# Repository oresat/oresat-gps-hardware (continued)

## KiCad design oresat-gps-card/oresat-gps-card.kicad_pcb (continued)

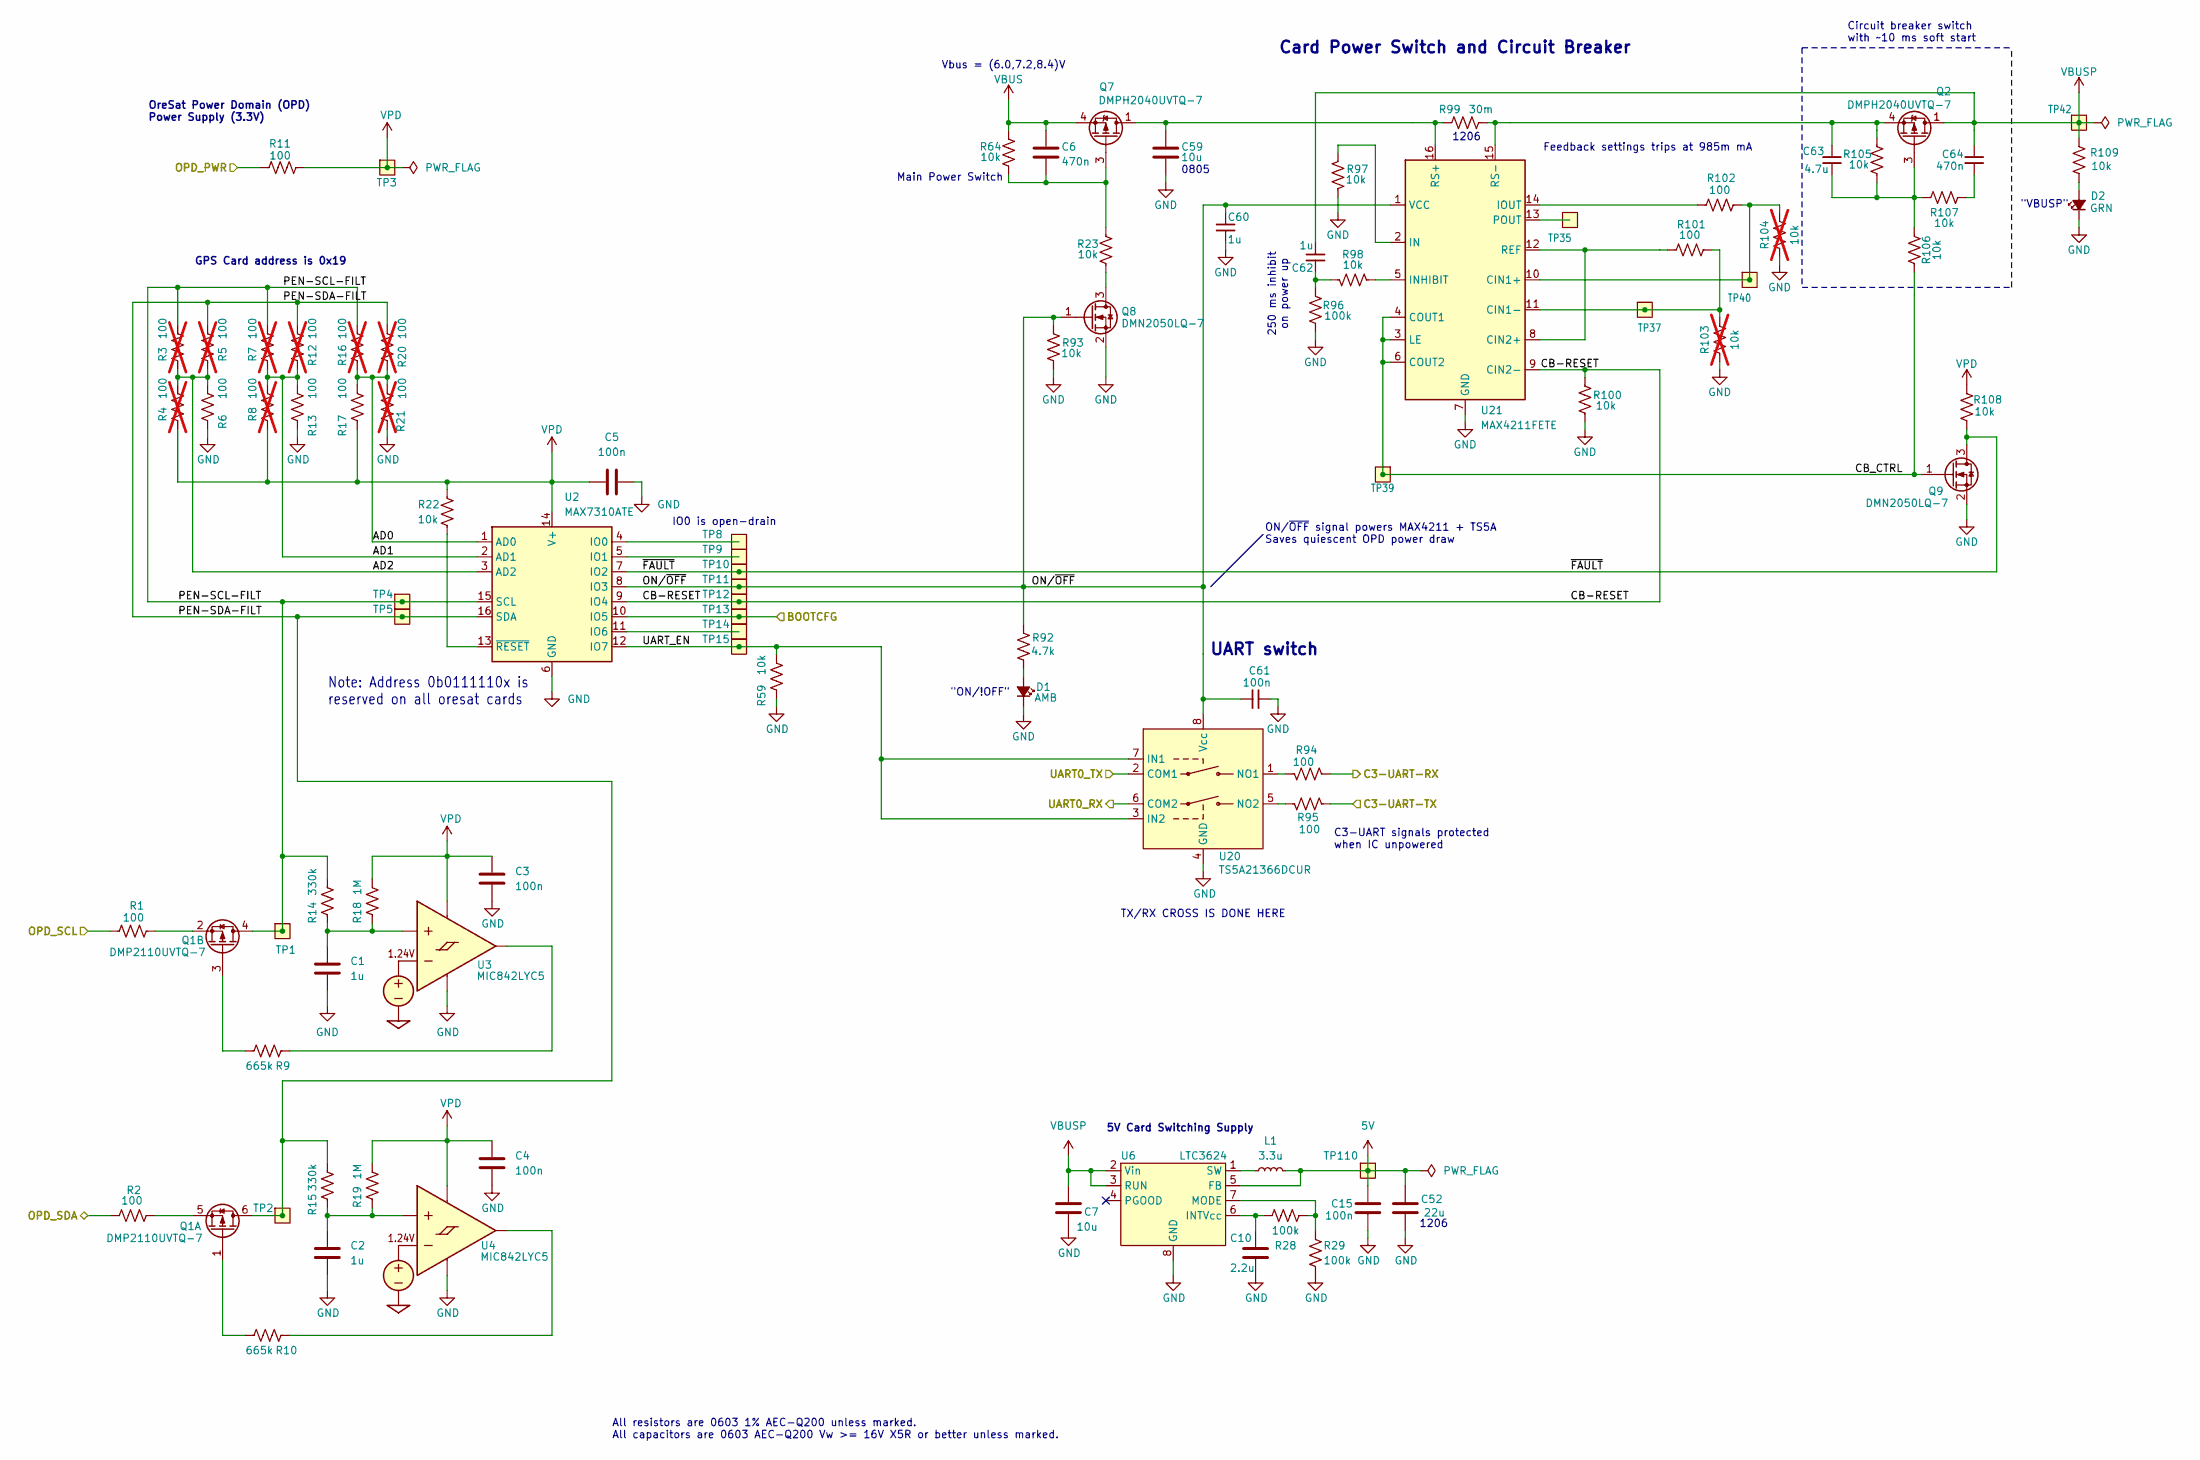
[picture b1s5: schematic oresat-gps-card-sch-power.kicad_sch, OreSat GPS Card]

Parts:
C1, C2, C60, C62: 1u; 0603-C-NOSILK; MPN GRT188R71E105KE13D
C3, C4, C5, C15, C61: 100n; 0603-C-NOSILK; MPN C0603C104K5RACAUTO
C6, C64: 470n; 0603-C-NOSILK; MPN C0603C474K3RACAUTO
C7: 10u; 0805-C-NOSILK; MPN GRT21BC71E106KE13K
C10: 2.2u; 0603-C-NOSILK; MPN GRT188C71E225KE13D
C52: 22u; C_1206_3216Metric; MPN GRT31CC81C226KE01L
C59: 10u; 0805-B-NOSILK; MPN GRT21BC71E106KE13K
C63: 4.7u; 0603-C-NOSILK; MPN GRT21BC71E475KE13L
D1: AMB; LED_0603_1608Metric; MPN 150060AS75000
D2: GRN; LED_0603_1608Metric; MPN 150060GS75000
L1: 3.3u; L_ECS-MPI4040; MPN ECS-MPIP0420-3R3MC
Q1: DMP2110UVTQ-7; SOT-23-6; MPN DMP2110UVTQ-7
Q2, Q7: DMPH2040UVTQ-7; TSOT-23-6; MPN DMPH2040UVTQ-7
Q8, Q9: DMN2050LQ-7; SOT-23; MPN DMN2050LQ-7
R1, R2, R6, R11, R13, R17, R94, R95, R101, R102: 100; 0603-C-NOSILK; MPN RMCF0603FT100R
R3, R4, R5, R7, R8, R12, R16, R20, R21: 100; 0603-C-NOSILK; not fitted
R9, R10: 665k; 0603-C-NOSILK; MPN RMCF0603FT665K
R14, R15: 330k; 0603-C-NOSILK; MPN RMCF0603FT330K
R18, R19: 1M; 0603-C-NOSILK; MPN RMCF0603FT1M00
R22, R23, R59, R64, R93, R97, R98, R100, R105, R106, R107, R108, R109: 10k; 0603-C-NOSILK; MPN RMCF0603FT10K0
R28, R29, R96: 100k; 0603-C-NOSILK; MPN RMCF0603FT100K
R92: 4.7k; 0603-C-NOSILK; MPN RMCF0603FT4K70
R99: 30m; 1206-C; MPN CSR1206FK30L0
R103, R104: 10k; 0603-C-NOSILK; MPN RMCF0603FT10K0; not fitted
TP1, TP2, TP3, TP4, TP5, TP8, TP9, TP10, TP11, TP12, TP13, TP14, TP15, TP35, TP37, TP39, TP40, TP42, TP110: Test-Point; TestPoint-0.75mm-th
U2: MAX7310ATE; QFN-16-1EP_4x4mm_P0.65mm_EP2.1x2.1mm; MPN MAX7310ATE+
U3, U4: MIC842LYC5; SOT-353_SC-70-5; MPN MIC842LYC5-TR
U6: LTC3624; DFN-8-1EP_3x3mm_P0.5mm_EP1.65x2.38mm_ThermalVias0.3mm; MPN LTC3624IDD-5#PBF
U20: TS5A21366DCUR; VSSOP-8_2.3x2mm_P0.5mm; MPN TS5A21366DCUR
U21: MAX4211FETE; QFN-16-1EP_4x4mm_P0.65mm_EP2.1x2.1mm; MPN MAX4211FETE

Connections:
5V: C15.1, C52.1, L1.2, TP110.1 (1_1), U6.5 (FB); also elsewhere on the board
/C3-UART-RX: R94.1; also elsewhere on the board
/C3-UART-TX: R95.1; also elsewhere on the board
/OPD_PWR: R11.1; also elsewhere on the board
/OPD_SCL: R1.1; also elsewhere on the board
/OPD_SDA: R2.1; also elsewhere on the board
/OSD3358 SYSBOOT : SIP D/BOOTCFG: TP13.1 (1_1), U2.10 (IO5); also elsewhere on the board
/Power/AD0: R16.2, R17.1, R20.2, R21.1, U2.1 (AD0)
/Power/AD1: R7.2, R8.1, R12.2, R13.1, U2.2 (AD1)
/Power/AD2: R3.2, R4.1, R5.2, R6.1, U2.3 (AD2)
/Power/CB-RESET: R100.2, TP12.1 (1_1), U2.9 (IO4), U21.9 (CIN2-)
/Power/CB_CTRL: Q9.1 (G), R106.1, TP39.1 (1_1), U21.3 (LE), U21.4 (COUT1), U21.6 (COUT2)
/Power/ON/~OFF: C60.1, C61.2, Q8.1 (G), R92.1, R93.2, TP11.1 (1_1), U2.8 (IO3), U20.8 (Vcc), U21.1 (VCC)
/Power/PEN-SCL-FILT: Q1.4 (D), R3.1, R7.1, R14.2, R16.1, TP1.1 (1_1), TP4.1 (1_1), U2.15 (SCL)
/Power/PEN-SDA-FILT: Q1.6 (D), R5.1, R12.1, R15.2, R20.1, TP2.1 (1_1), TP5.1 (1_1), U2.16 (SDA)
/Power/UART_EN: R59.2, TP15.1 (1_1), U2.12 (IO7), U20.3 (IN2), U20.7 (IN1)
/Power/~FAULT: Q9.3 (D), R108.1, TP10.1 (1_1), U2.7 (IO2)
/UART0_RX: U20.6 (COM2); also elsewhere on the board
/UART0_TX: U20.2 (COM1); also elsewhere on the board
GND: C1.1, C2.1, C3.1, C4.1, C5.2, C7.2, C10.2, C15.2, C52.2, C59.2, C60.2, C61.1, D1.1 (K), D2.1 (K), Q8.2 (S), Q9.2 (S), R6.2, R13.2, R21.2, R29.2, R59.1, R93.1, R96.1, R97.2, R100.1, R103.1, R104.1, U2.6 (GND), U2.17 (GND), U3.2 (GND), U4.2 (GND), U6.8 (GND), U6.9 (GND), U20.4 (GND), U21.7 (GND), U21.17 (GND); also elsewhere on the board
unnamed: C62.1, R96.2, R98.2
unnamed: C64.1, R107.1
unnamed: D1.2 (A), R92.2
unnamed: D2.2 (A), R109.1
unnamed: Q1.1 (G), R10.2
unnamed: Q1.5 (S), R2.2
unnamed: Q1.3 (G), R9.2
unnamed: Q1.2 (S), R1.2
unnamed: C63.1, Q2.3 (G), R105.1, R106.2, R107.2
unnamed: C63.2, Q2.4 (S), R99.2, R105.2, U21.15 (RS-)
unnamed: C6.2, Q7.3 (G), R23.2, R64.1
unnamed: Q8.3 (D), R23.1
unnamed: TP8.1 (1_1), U2.4 (IO0)
unnamed: TP9.1 (1_1), U2.5 (IO1)
unnamed: TP14.1 (1_1), U2.11 (IO6)
unnamed: R22.2, U2.13 (~RESET)
unnamed: C1.2, R14.1, R18.1, U3.1 (INP)
unnamed: R9.1, U3.4 (OUT)
unnamed: C2.2, R15.1, R19.1, U4.1 (INP)
unnamed: R10.1, U4.4 (OUT)
unnamed: C10.1, R28.1, U6.6 (INTVcc)
unnamed: R28.2, R29.1, U6.7 (MODE)
unnamed: L1.1, U6.1 (SW)
unnamed: R94.2, U20.1 (NO1)
unnamed: R95.2, U20.5 (NO2)
unnamed: R102.1, R104.2, TP40.1 (1_1), U21.10 (CIN1+)
unnamed: R101.1, R103.2, TP37.1 (1_1), U21.11 (CIN1-)
unnamed: R101.2, U21.8 (CIN2+), U21.12 (REF)
unnamed: R97.1, U21.2 (IN)
unnamed: R98.1, U21.5 (INHIBIT)
unnamed: R102.2, U21.14 (IOUT)
unnamed: TP35.1 (1_1), U21.13 (POUT)
unnamed: C59.1, Q7.1 (D), Q7.2 (D), Q7.5 (D), Q7.6 (D), R99.1, U21.16 (RS+)
VBUS: C6.1, Q7.4 (S), R64.2; also elsewhere on the board
VBUSP: C7.1, C62.2, C64.2, Q2.1 (D), Q2.2 (D), Q2.5 (D), Q2.6 (D), R109.2, TP42.1 (1_1), U6.2 (Vin), U6.3 (RUN)
VPD: C3.2, C4.2, C5.1, R4.2, R8.2, R11.2, R17.2, R18.2, R19.2, R22.1, R108.2, TP3.1 (1_1), U2.14 (V+), U3.5 (VDD), U4.5 (VDD)

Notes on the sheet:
Circuit breaker switch with ~10 ms soft start
Main Power Switch
5V Card Switching Supply
IO0 is open-drain
OreSat Power Domain (OPD) Power Supply (3.3V)
Feedback settings trips at 985m mA
TX/RX CROSS IS DONE HERE
"ON/!OFF"
1206
Vbus = (6.0,7.2,8.4)V
Note: Address 0b0111110x is reserved on all oresat cards
0805
GPS Card address is 0x19
C3-UART signals protected when IC unpowered
All resistors are 0603 1% AEC-Q200 unless marked. All capacitors are 0603 AEC-Q200 Vw >= 16V X5R or better unless marked.
"VBUSP"
Card Power Switch and Circuit Breaker
250 ms inhibit on power up
UART switch
ON/~{OFF} signal powers MAX4211 + TS5A Saves quiescent OPD power draw

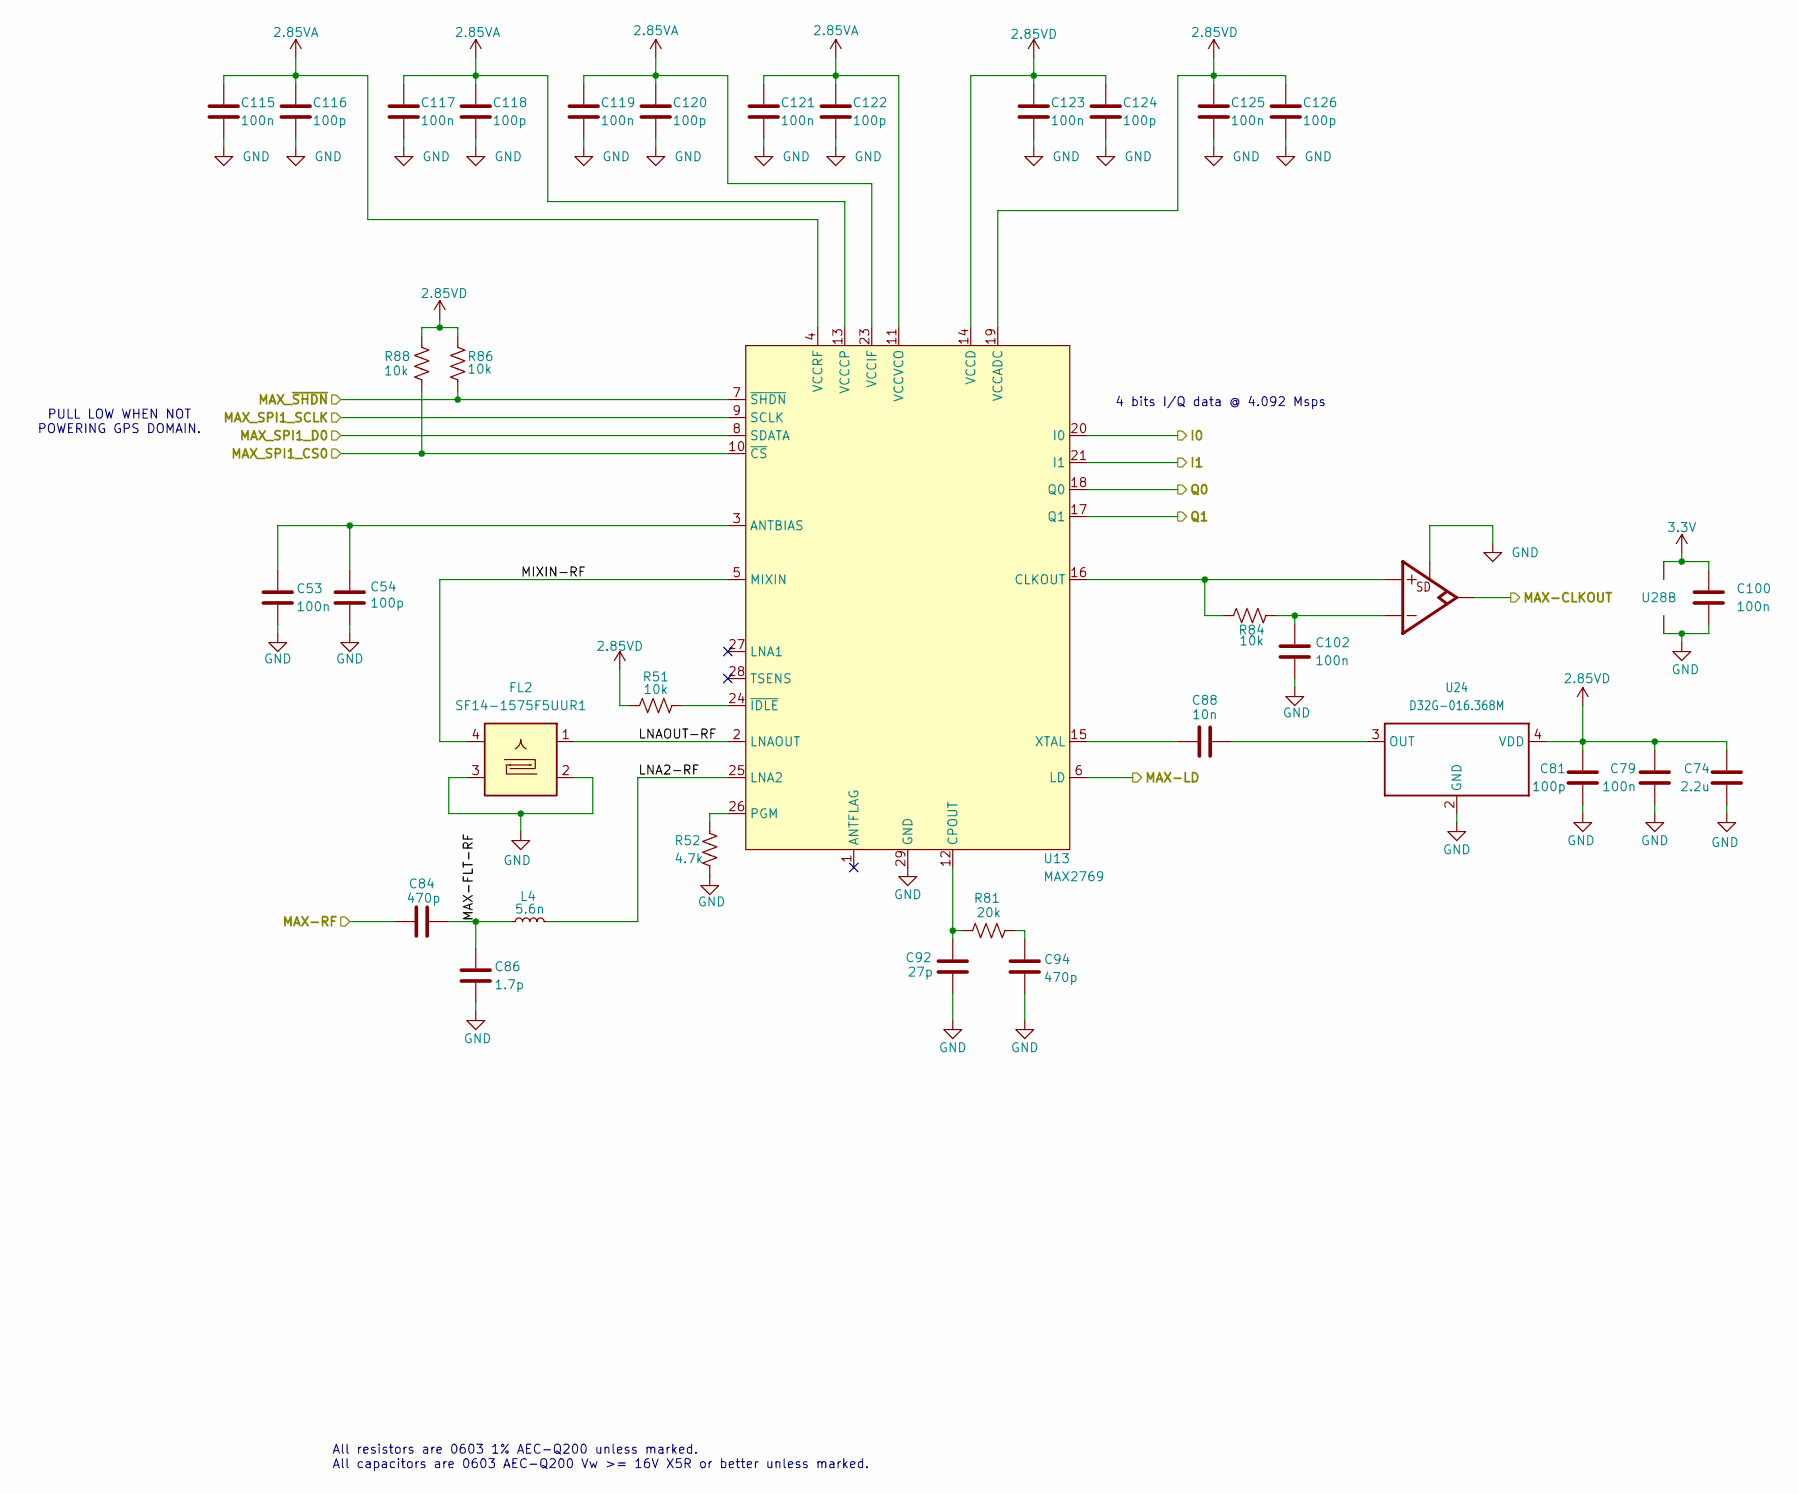
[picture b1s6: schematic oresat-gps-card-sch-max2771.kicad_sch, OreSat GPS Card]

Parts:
C53, C79, C100, C102, C115, C117, C119, C121, C123, C125: 100n; 0603-C-NOSILK; MPN C0603C104K5RACAUTO
C54, C81, C116, C118, C120, C122, C124, C126: 100p; 0603-C-NOSILK; MPN C0603C101K5HACAUTO
C74: 2.2u; 0603-C-NOSILK; MPN GRT188C71E225KE13D
C84, C94: 470p; 0603-C-NOSILK; MPN C0603C471K5RACAUTO
C86: 1.7p; 0603-C-NOSILK; MPN GRM1885C1H1R7BA01D
C88: 10n; 0603-C-NOSILK; MPN C0603C103J5RACAUTO
C92: 27p; 0603-C-NOSILK; MPN GCM1885C2A270JA16D
FL2: SF14-1575F5UUR1; Filter_1411-5_1.4x1.1mm; MPN SF14-1575F5UUR1
L4: 5.6n; 0603-C-NOSILK; MPN LQG18HN5N6S00D
R51, R84, R86, R88: 10k; 0603-C-NOSILK; MPN RMCF0603FT10K0
R52: 4.7k; 0603-C-NOSILK; MPN RMCF0603FT4K70
R81: 20k; 0603-C-NOSILK; MPN RMCF0603FT20K0
U13: MAX2769; TQFN-28-1EP_5x5mm_P0.5mm_EP3.25x3.25mm; MPN MAX2769BETI/V+T
U24: D32G-016.368M; U-Connor-Winfield-D32G-016368M
U28: LT1719IS6; SOT-23-6

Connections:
2.85VA: C115.1, C116.1, C117.1, C118.1, C119.1, C120.1, C121.1, C122.1, U13.4 (VCCRF), U13.11 (VCCVCO), U13.13 (VCCCP), U13.23 (VCCIF); also elsewhere on the board
2.85VD: C74.1, C79.1, C81.1, C123.1, C124.1, C125.1, C126.1, R51.1, R86.1, R88.2, U13.14 (VCCD), U13.19 (VCCADC), U24.4 (VDD); also elsewhere on the board
3.3V: C100.1, U28.4 (V+); also elsewhere on the board
/MAX2769/I0: U13.20 (I0); also elsewhere on the board
/MAX2769/I1: U13.21 (I1); also elsewhere on the board
/MAX2769/LNA2-RF: L4.2, U13.25 (LNA2)
/MAX2769/LNAOUT-RF: FL2.1, U13.2 (LNAOUT)
/MAX2769/MAX-CLKOUT: U28.5 (OUT); also elsewhere on the board
/MAX2769/MAX-FLT-RF: C84.2, C86.1, L4.1
/MAX2769/MAX-LD: U13.6 (LD); also elsewhere on the board
/MAX2769/MAX-RF: C84.1; also elsewhere on the board
/MAX2769/MAX_SPI1_CS0: R88.1, U13.10 (~CS); also elsewhere on the board
/MAX2769/MAX_SPI1_D0: U13.8 (SDATA); also elsewhere on the board
/MAX2769/MAX_SPI1_SCLK: U13.9 (SCLK); also elsewhere on the board
/MAX2769/MAX_~SHDN: R86.2, U13.7 (~SHDN); also elsewhere on the board
/MAX2769/MIXIN-RF: FL2.4, U13.5 (MIXIN)
/MAX2769/Q0: U13.18 (Q0); also elsewhere on the board
/MAX2769/Q1: U13.17 (Q1); also elsewhere on the board
GND: C53.2, C54.2, C74.2, C79.2, C81.2, C86.2, C92.1, C94.1, C100.2, C102.2, C115.2, C116.2, C117.2, C118.2, C119.2, C120.2, C121.2, C122.2, C123.2, C124.2, C125.2, C126.2, FL2.2, FL2.3, FL2.5, R52.2, U13.29 (GND), U24.2 (GND), U28.2 (V-), U28.6 (SD); also elsewhere on the board
unnamed: C94.2, R81.1
unnamed: C53.1, C54.1, U13.3 (ANTBIAS)
unnamed: R84.2, U13.16 (CLKOUT), U28.3 (+IN)
unnamed: C92.2, R81.2, U13.12 (CPOUT)
unnamed: R52.1, U13.26 (PGM)
unnamed: C88.2, U13.15 (XTAL)
unnamed: R51.2, U13.24 (~IDLE)
unnamed: C88.1, U24.3 (OUT)
unnamed: C102.1, R84.1, U28.1 (-IN)

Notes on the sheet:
All resistors are 0603 1% AEC-Q200 unless marked. All capacitors are 0603 AEC-Q200 Vw >= 16V X5R or better unless marked.
PULL LOW WHEN NOT POWERING GPS DOMAIN.
4 bits I/Q data @ 4.092 Msps

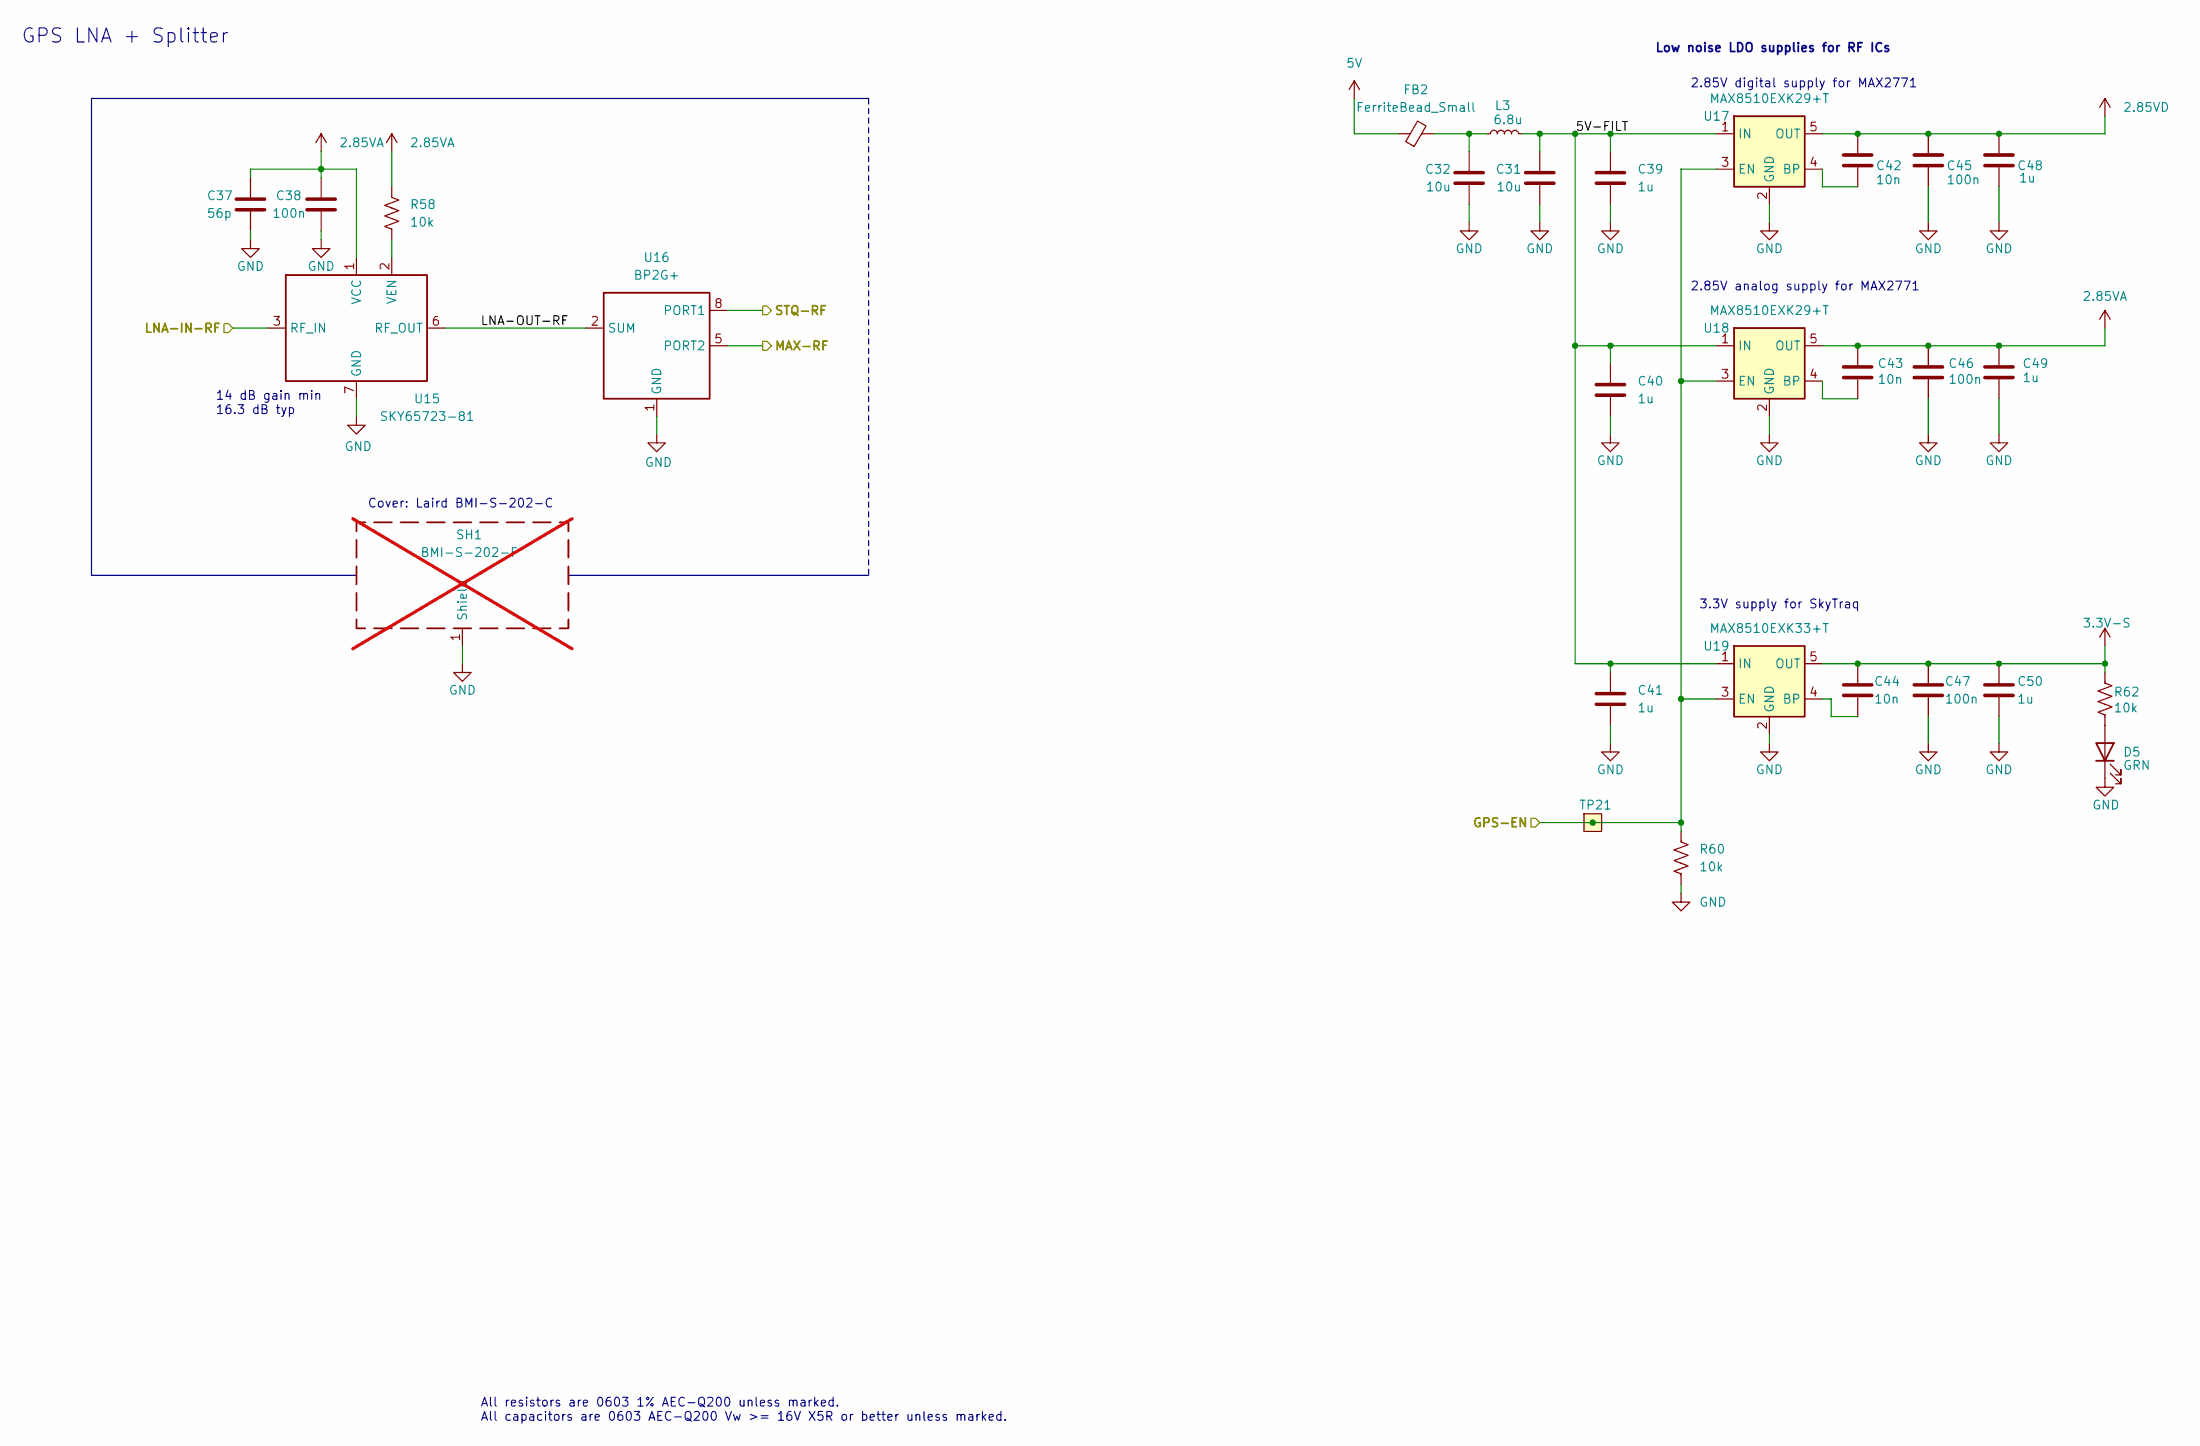
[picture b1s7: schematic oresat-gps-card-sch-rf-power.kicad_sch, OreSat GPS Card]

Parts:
C31, C32: 10u; 0805-C-NOSILK; MPN GRT21BC71E106KE13K
C37: 56p; 0603-C-NOSILK; MPN GRM1885C2A560JA01D
C38, C45, C46, C47: 100n; 0603-C-NOSILK; MPN C0603C104K5RACAUTO
C39, C40, C41, C48, C49, C50: 1u; 0603-C-NOSILK; MPN GRT188R71E105KE13D
C42, C43, C44: 10n; 0603-C-NOSILK; MPN C0603C103J5RACAUTO
D5: GRN; LED_0603_1608Metric; MPN 150060GS75000
FB2: FerriteBead_Small; 0805-C-NOSILK; MPN BLM21PG331SN1D
L3: 6.8u; L_ECS-MPI4040; MPN ECS-MPIP0420-6R8MC
R58, R60, R62: 10k; 0603-C-NOSILK; MPN RMCF0603FT10K0
SH1: BMI-S-202-F; Laird_Technologies_BMI-S-202-F_16.50x16.50mm; MPN BMI-S-202-F; not fitted
TP21: Test-Point; TestPoint-0.75mm-th
U15: SKY65723-81; U-Skyworks-SKY65723-81-gps-lna; MPN SKY65723-81
U16: BP2G+; U-Minicircuits-BP2G+; MPN BP2G1+
U17, U18: MAX8510EXK29+T; SOT-353_SC-70-5; MPN MAX8510EXK29+T
U19: MAX8510EXK33+T; SOT-353_SC-70-5; MPN MAX8510EXK33+T

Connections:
2.85VA: C37.1, C38.1, C43.1, C46.1, C49.1, R58.1, U15.1 (VCC), U18.5 (OUT); also elsewhere on the board
2.85VD: C42.1, C45.1, C48.1, U17.5 (OUT); also elsewhere on the board
3.3V-S: C44.1, C47.1, C50.1, R62.2, U19.5 (OUT); also elsewhere on the board
5V: FB2.1; also elsewhere on the board
/LNA-IN-RF: U15.3 (RF_IN); also elsewhere on the board
/MAX2769/MAX-RF: U16.5 (PORT2); also elsewhere on the board
/OSD3358 SYSBOOT : SIP D/GPS-EN: R60.1, TP21.1 (1_1), U17.3 (EN), U18.3 (EN), U19.3 (EN); also elsewhere on the board
/RF + RF Power/5V-FILT: C31.1, C39.1, C40.1, C41.1, L3.2, U17.1 (IN), U18.1 (IN), U19.1 (IN)
/RF + RF Power/LNA-OUT-RF: U15.6 (RF_OUT), U16.2 (SUM)
/RF + RF Power/STQ-RF: U16.8 (PORT1); also elsewhere on the board
GND: C31.2, C32.2, C37.2, C38.2, C39.2, C40.2, C41.2, C45.2, C46.2, C47.2, C48.2, C49.2, C50.2, D5.1 (K), R60.2, SH1.1 (Shield_1), U15.7 (GND), U16.1 (GND), U16.3 (GND), U16.4 (GND), U16.6 (GND), U16.7 (GND), U17.2 (GND), U18.2 (GND), U19.2 (GND); also elsewhere on the board
unnamed: C32.1, FB2.2, L3.1
unnamed: D5.2 (A), R62.1
unnamed: R58.2, U15.2 (VEN)
unnamed: C42.2, U17.4 (BP)
unnamed: C43.2, U18.4 (BP)
unnamed: C44.2, U19.4 (BP)

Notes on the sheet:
3.3V supply for SkyTraq
Cover: Laird BMI-S-202-C
All resistors are 0603 1% AEC-Q200 unless marked. All capacitors are 0603 AEC-Q200 Vw >= 16V X5R or better unless marked.
2.85V digital supply for MAX2771
Low noise LDO supplies for RF ICs
2.85V analog supply for MAX2771
14 dB gain min 16.3 dB typ
GPS LNA + Splitter

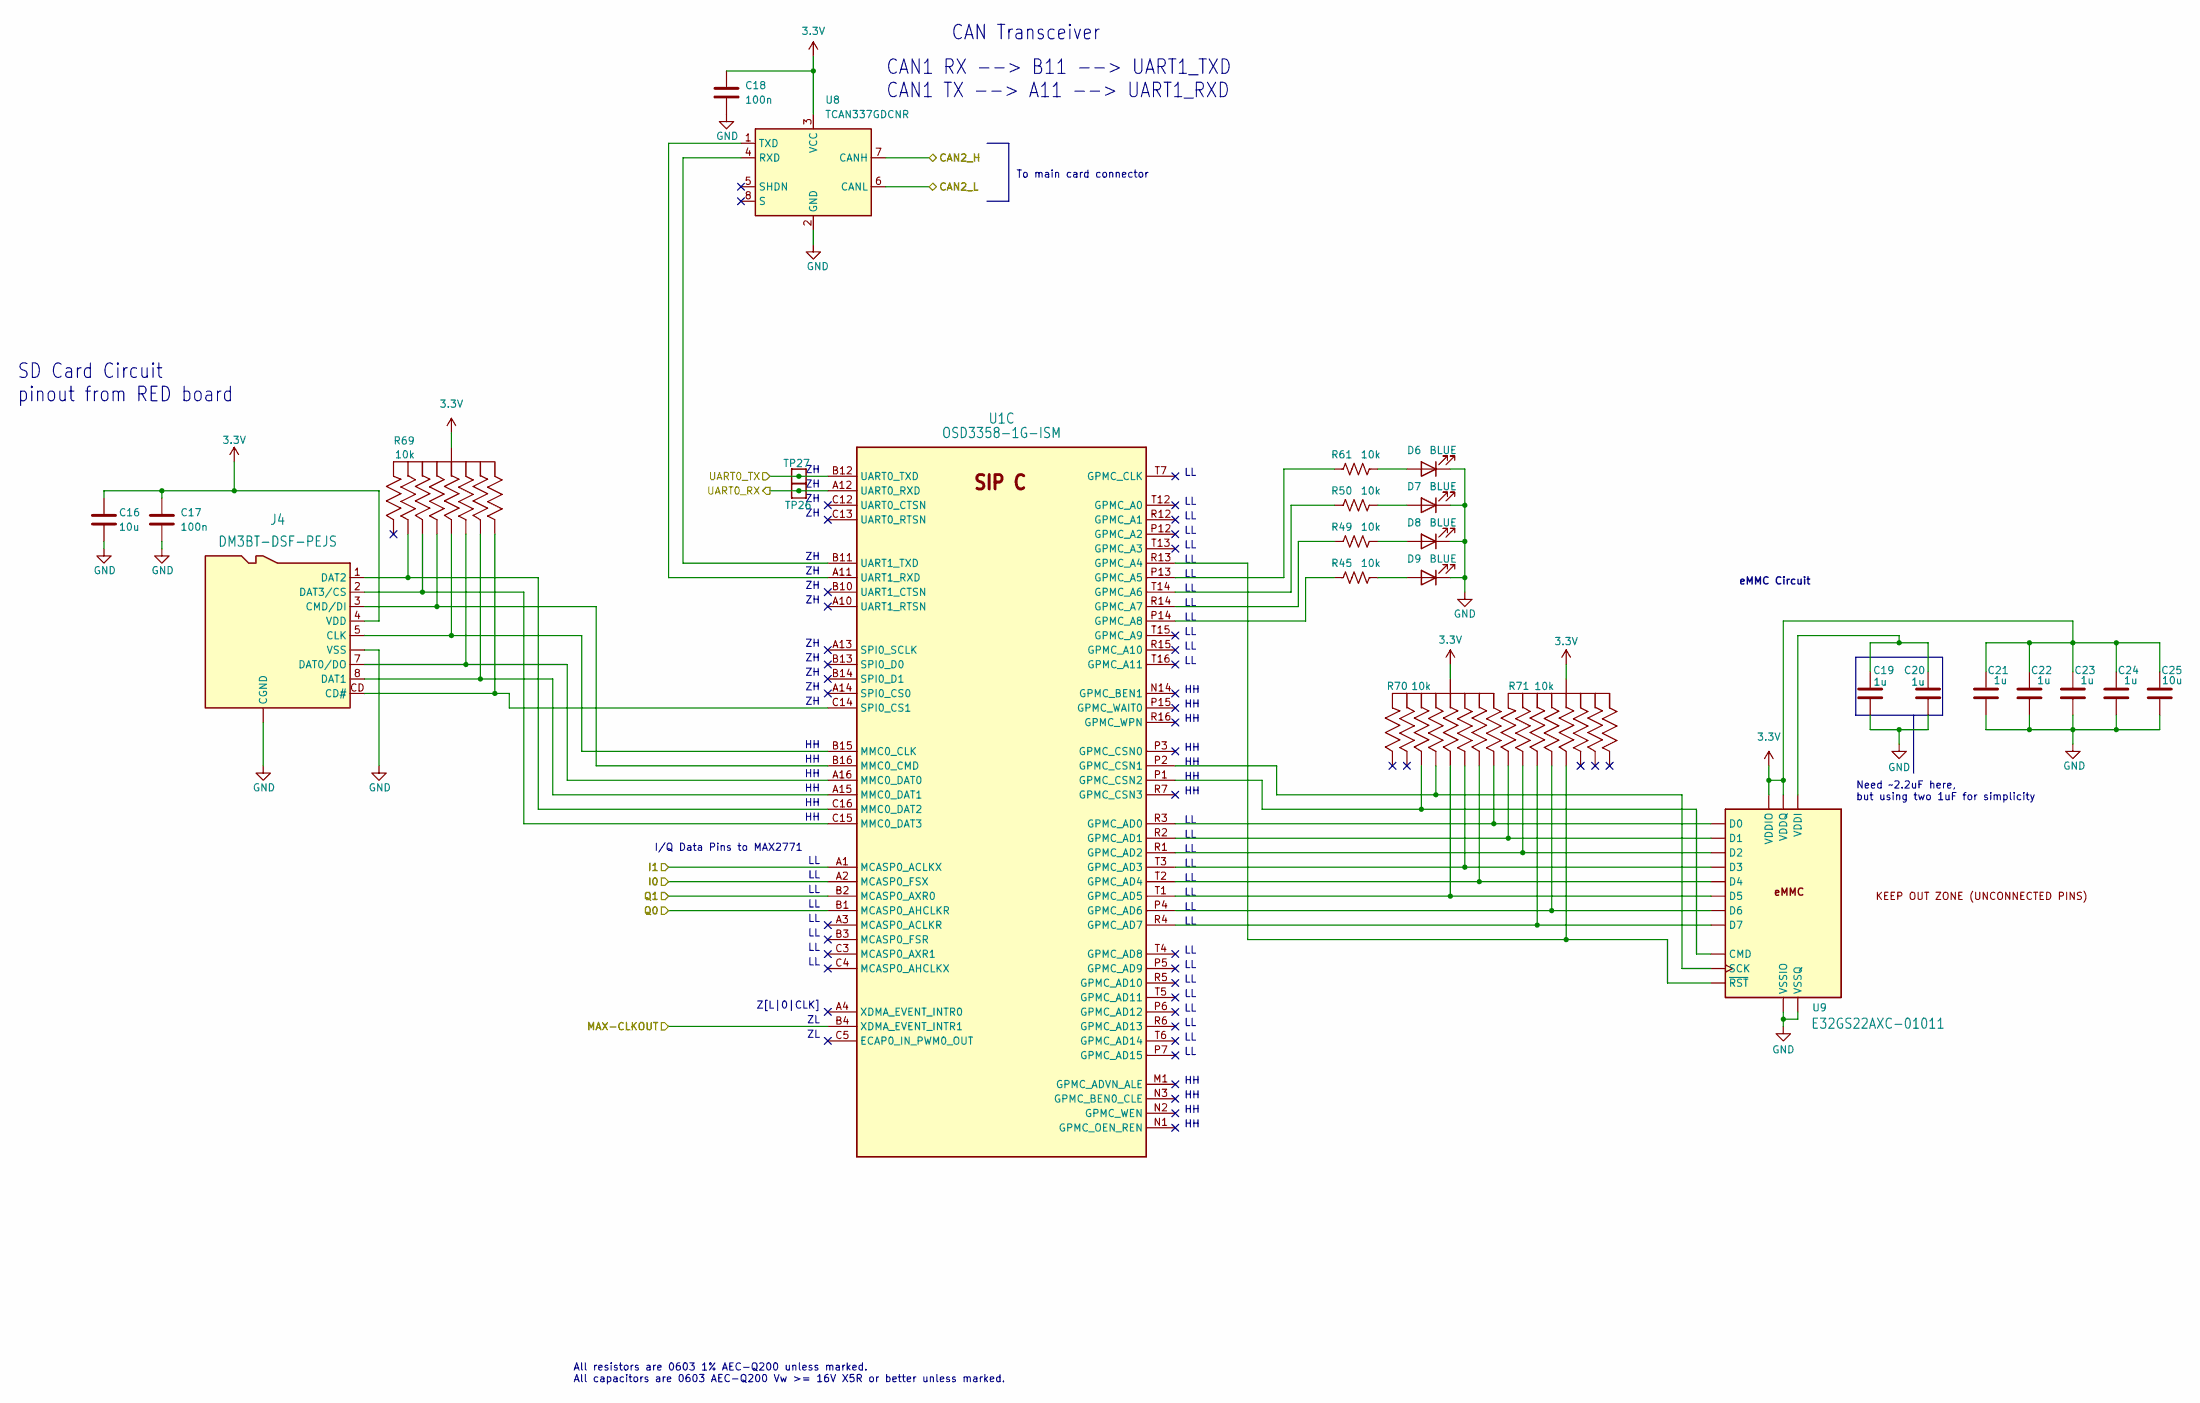
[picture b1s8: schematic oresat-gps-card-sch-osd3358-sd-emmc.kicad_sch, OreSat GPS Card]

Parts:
C16, C25: 10u; 0805-C-NOSILK; MPN GRT21BC71E106KE13K
C17, C18: 100n; 0603-C-NOSILK; MPN C0603C104K5RACAUTO
C19, C20, C21, C22, C23, C24: 1u; 0603-C-NOSILK; MPN GRT188R71E105KE13D
D6, D7, D8, D9: BLUE; LED_0603_1608Metric; MPN 150060BS75000
J4: DM3BT-DSF-PEJS; J-Hirose-DM3BT-DSF-PEJS; MPN DM3BT-DSF-PEJS
R45, R49, R50, R61: 10k; 0603-C-NOSILK; MPN RMCF0603FT10K0
R69, R70, R71: 10k; Panasonic_Resistor_Array_EXBA10; MPN EXB-A10P103J
TP26, TP27: Test-Point; TestPoint-0.75mm-th
U1: OSD3358-1G-ISM; U-Octavo-OSD335X-BGA-256; MPN OSD3358-1G-ISM
U8: TCAN337GDCNR; SOT-23-8; MPN TCAN337GDCNR
U9: E32GS22AXC-01011; BGA-153(11.5X13)(EMMC-BA); MPN E32GS22AXC-01011

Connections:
3.3V: C16.1, C17.1, C18.1, C21.1, C22.1, C23.1, C24.1, C25.1, J4.4 (VDD), R69.5 (55), R69.10 (55), R70.5 (55), R70.10 (55), R71.5 (55), R71.10 (55), U8.3 (VCC), U9.C6 (VDDQ), U9.E6 (VDDIO), U9.F5 (VDDIO), U9.J10 (VDDIO), U9.K9 (VDDIO), U9.M4 (VDDQ), U9.N4 (VDDQ), U9.P3 (VDDQ), U9.P5 (VDDQ); also elsewhere on the board
/CAN2_H: U8.7 (CANH); also elsewhere on the board
/CAN2_L: U8.6 (CANL); also elsewhere on the board
/MAX2769/I0: U1.A2 (MCASP0_FSX); also elsewhere on the board
/MAX2769/I1: U1.A1 (MCASP0_ACLKX); also elsewhere on the board
/MAX2769/MAX-CLKOUT: U1.B4 (XDMA_EVENT_INTR1); also elsewhere on the board
/MAX2769/Q0: U1.B1 (MCASP0_AHCLKR); also elsewhere on the board
/MAX2769/Q1: U1.B2 (MCASP0_AXR0); also elsewhere on the board
/UART0_RX: TP26.1 (1_1), U1.A12 (UART0_RXD); also elsewhere on the board
/UART0_TX: TP27.1 (1_1), U1.B12 (UART0_TXD); also elsewhere on the board
GND: C16.2, C17.2, C18.2, C19.2, C20.2, C21.2, C22.2, C23.2, C24.2, C25.2, D6.1 (K), D7.1 (K), D8.1 (K), D9.1 (K), J4.6 (VSS), J4.CGND1 (CGND), J4.CGND2 (CGND), J4.CGND3 (CGND), J4.CGND4 (CGND), J4.CGND5 (CGND), J4.CGND6 (CGND), J4.GND (VSS), U8.2 (GND), U9.A6 (VSSIO), U9.C4 (VSSQ), U9.E7 (VSSIO), U9.G5 (VSSIO), U9.H10 (VSSIO), U9.J5 (VSSIO), U9.K8 (VSSIO), U9.N2 (VSSQ), U9.N5 (VSSQ), U9.P4 (VSSQ), U9.P6 (VSSQ); also elsewhere on the board
unnamed: D6.2 (A), R61.2
unnamed: D7.2 (A), R50.2
unnamed: D8.2 (A), R49.2
unnamed: D9.2 (A), R45.2
unnamed: J4.CD (CD#), R69.6 (66), U1.C14 (SPI0_CS1)
unnamed: J4.5 (CLK), R69.3 (33), U1.B15 (MMC0_CLK)
unnamed: J4.3 (CMD/DI), R69.8 (88), U1.B16 (MMC0_CMD)
unnamed: J4.7 (DAT0/DO), R69.7 (77), U1.A16 (MMC0_DAT0)
unnamed: J4.8 (DAT1), R69.4 (44), U1.A15 (MMC0_DAT1)
unnamed: J4.1 (DAT2), R69.9 (99), U1.C16 (MMC0_DAT2)
unnamed: J4.2 (DAT3/CS), R69.2 (22), U1.C15 (MMC0_DAT3)
unnamed: R70.2 (22), U1.P1 (GPMC_CSN2), U9.M5 (CMD)
unnamed: R70.3 (33), U1.T1 (GPMC_AD5), U9.B4 (D5)
unnamed: R70.4 (44), U1.T2 (GPMC_AD4), U9.B3 (D4)
unnamed: R70.6 (66), U1.R3 (GPMC_AD0), U9.A3 (D0)
unnamed: R70.7 (77), U1.T3 (GPMC_AD3), U9.B2 (D3)
unnamed: R70.8 (88), U1.P2 (GPMC_CSN1), U9.M6 (SCK)
unnamed: R71.1 (11), U1.R2 (GPMC_AD1), U9.A4 (D1)
unnamed: R71.2 (22), U1.R4 (GPMC_AD7), U9.B6 (D7)
unnamed: R71.3 (33), U1.R13 (GPMC_A4), U9.K5 (~RST)
unnamed: R71.8 (88), U1.P4 (GPMC_AD6), U9.B5 (D6)
unnamed: R71.9 (99), U1.R1 (GPMC_AD2), U9.A5 (D2)
unnamed: R61.1, U1.P13 (GPMC_A5)
unnamed: R50.1, U1.T14 (GPMC_A6)
unnamed: R49.1, U1.R14 (GPMC_A7)
unnamed: R45.1, U1.P14 (GPMC_A8)
unnamed: U1.A11 (UART1_RXD), U8.1 (TXD)
unnamed: U1.B11 (UART1_TXD), U8.4 (RXD)
unnamed: C19.1, C20.1, U9.C2 (VDDI)

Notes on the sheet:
CAN1 RX --> B11 --> UART1_TXD CAN1 TX --> A11 --> UART1_RXD
I/Q Data Pins to MAX2771
eMMC Circuit
All resistors are 0603 1% AEC-Q200 unless marked. All capacitors are 0603 AEC-Q200 Vw >= 16V X5R or better unless marked.
SD Card Circuit pinout from RED board
Need ~2.2uF here, but using two 1uF for simplicity
Z[L|0|CLK]
CAN Transceiver
To main card connector

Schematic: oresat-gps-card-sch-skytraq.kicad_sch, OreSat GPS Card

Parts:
C65, C75: 100n; 0603-C-NOSILK; MPN C0603C104K5RACAUTO
C76: 1u; 0603-C-NOSILK; MPN GRT188R71E105KE13D
C77: 100p; 0603-C-NOSILK; MPN C0603C101K5HACAUTO
R65: 10k; 0603-C-NOSILK; MPN RMCF0603FT10K0
R66, R67: 100; 0603-C-NOSILK; MPN RMCF0603FT100R
R80: NP; R_0603_1608Metric; not fitted
TP20, TP23, TP24: Test-Point; TestPoint-0.75mm-th
U22: TS5A21366DCUR; VSSOP-8_2.3x2mm_P0.5mm; MPN TS5A21366DCUR
U23: ORION-B16; U-SkyTraq-ORION-B16; MPN ORION B16

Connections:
3.3V-S: C65.2, C75.1, C76.1, C77.1, R65.1, U22.3 (IN2), U22.7 (IN1), U22.8 (Vcc), U23.22 (V_BCKP), U23.23 (VCC); also elsewhere on the board
/OSD3358 SYSBOOT : SIP D/STQ-1PPS: TP24.1 (1_1), U23.3 (1PPS); also elsewhere on the board
/OSD3358 SYSBOOT : SIP D/UART2_RX: U22.6 (COM2); also elsewhere on the board
/OSD3358 SYSBOOT : SIP D/UART2_TX: U22.2 (COM1); also elsewhere on the board
/RF + RF Power/STQ-RF: U23.11 (RF_IN); also elsewhere on the board
GND: C65.1, C75.2, C76.2, C77.2, R80.2, U22.4 (GND), U23.10 (GND), U23.12 (GND), U23.13 (GND), U23.24 (GND), U23.[10,12,13,24] (GND); also elsewhere on the board
unnamed: R66.1, TP20.1 (1_1), U22.1 (NO1)
unnamed: R67.1, TP23.1 (1_1), U22.5 (NO2)
unnamed: R80.1, U23.1 (BOOT_SEL)
unnamed: R65.2, U23.8 (RSTN)
unnamed: R66.2, U23.21 (RXD)
unnamed: R67.2, U23.20 (TXD)

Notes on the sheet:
All resistors are 0603 1% AEC-Q200 unless marked. All capacitors are 0603 AEC-Q200 Vw >= 16V X5R or better unless marked.
